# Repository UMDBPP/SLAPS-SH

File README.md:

# SLAPS-SH
The SLAPS Solar Harvester is intended as a the first step into solar power collection and management. While previous iterations in the SLAPS family have focused on solar panel deployment and configuration, the solar harvester focuses on collecting and managing the power generated by four solar panels. The primary device enabling this functionality is the AEM10941. This power harvesting IC collects power from the panels, regulates the power to multiple useful voltage levels, and charges a storage unit. This design required minimal passive components allowing for a low cost and space efficient design. In addition to the power harvesting circuit, the solar harvester will also feature a RP2040 microcontroller, altitude rated pressure-temperature sensor, and NAND flash for data logging. These additional components will provide an adequate test for the harvester capabilities. In order to leverage the space efficient nature of the electrical configuration, the structural construction of the solar harvester focuses on tight tolerances using 3D printed components. Maximizing the space efficiency of the solar harvester improves aesthetics and maximizes the flight line configurations that the solar harvester can fly on. Overall, this design will provide a realistic and maximally space efficient test of a solar harvesting circuit that could potentially be used in future SLAPS iterations.

## Electrical Overview
### AEM10941
The AEM10941 features multiple preset configurations as well as a custom mode. In this design, the configuration profile `111` is used by pulling the three configuration pins high. This configuration is designed for use with a Li-ion battery as the storage source and 3.3V and 1.8V outputs. The decision to use a Li-ion battery primarily comes from the need for a 3.3V output.

Quiescent current is expected to be roughly [0.6 \ \mu A](tex://0.6 \ \mu A) at a battery voltage of roughly 3.6V. The efficiency of the linear drop-out regulators are as follows:
- High-voltage: 80-90%
- Low-voltage: 70-80%

Overall, the losses experienced in the AEM10941 are relatively low in comparison to the power consumption of the device as a whole.

### RP2040
The RP2040 microcontroller is an incredibly popular Arduino compatible microcontroller with excellent design resources.

### MS560702BA03-50
The MS560702BA03-50 barometric pressure and temperature sensor designed to operate from [10](tex://10) to [1200 \ mbar](tex://1200 \ mbar) and [-40](tex://-40) to [85 \ \degree C](tex://85 \ \degree C). These values fall within typical launch conditions and this sensor should be able to provide barometric pressure and temperature values accurate to [\pm 2.5 mbar](tex://\pm 2.5 mbar) and [\pm 0.5 \ \degree C](tex://\pm 0.5 \ \degree C) for the duration of flight.

At a 3.3V supply voltage the MS560702BA03-50 has a peak power consumption of [4.62 \ mW](tex://4.62 \ mW) and a standby power consumption of [0.07 \ \mu W](tex://0.07 \ \mu W). Peak power consumption is unlikely to occur and typical power consumption at 1 sample/sec is expected to be less than [42 \ \mu W](tex://42 \ \mu W).

### Energy Storage
The solar harvester features one energy storage unit in the form of a single Li-ion battery cell.

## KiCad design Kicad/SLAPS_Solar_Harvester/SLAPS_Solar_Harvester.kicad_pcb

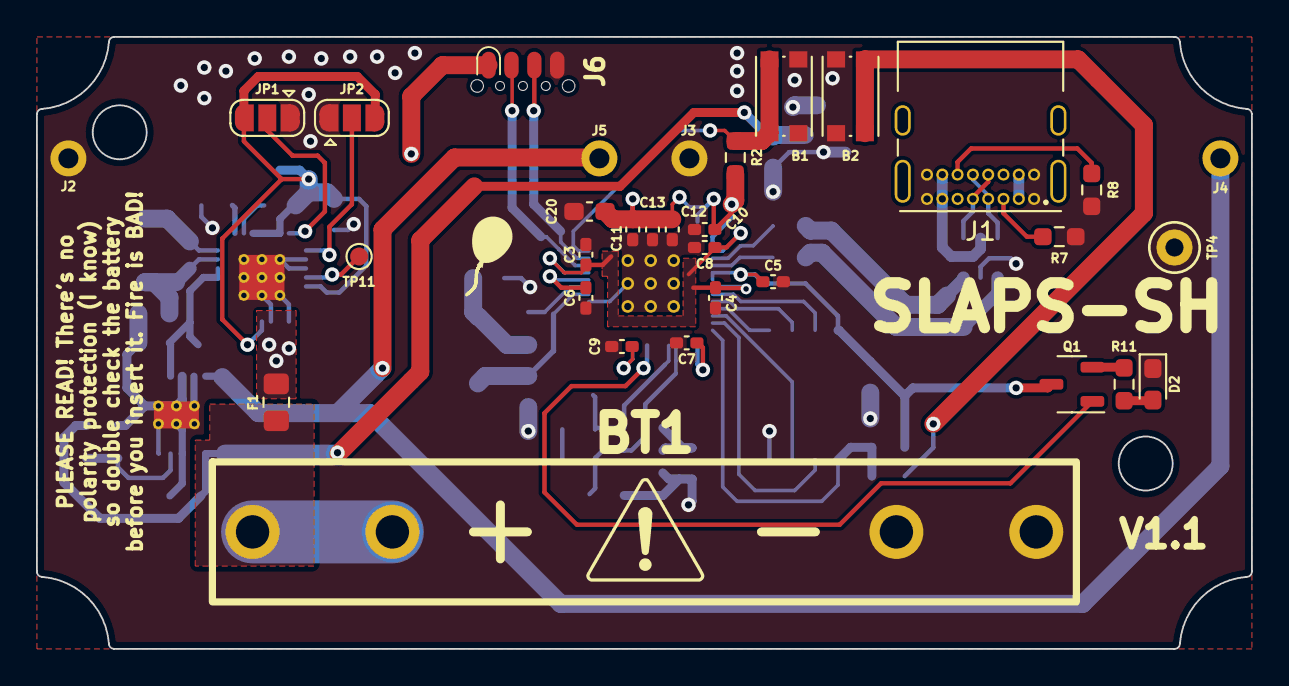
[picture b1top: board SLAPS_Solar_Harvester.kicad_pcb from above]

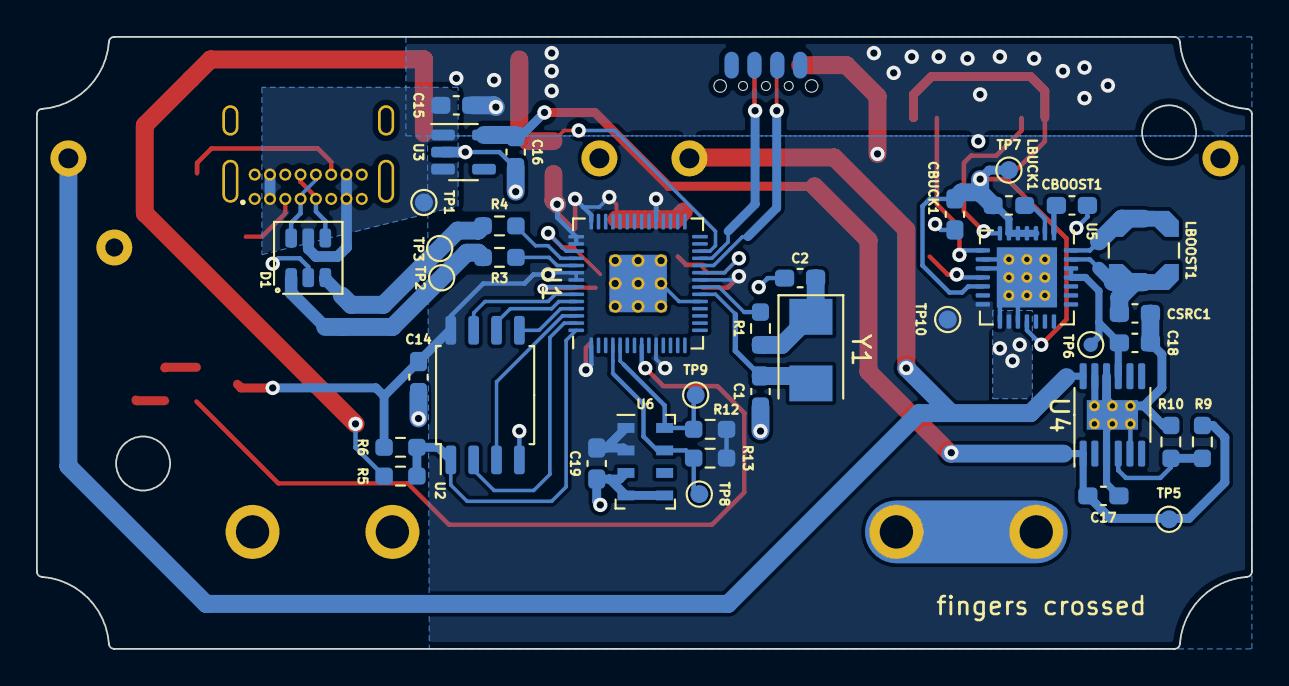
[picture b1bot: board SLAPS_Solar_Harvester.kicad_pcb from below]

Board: 2 copper layers, 67.5 x 34.0 mm, 71 parts (39 on the bottom side), 44 nets.

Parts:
B1, B2: KMR2; SW_Push_1P1T_NO_CK_KMR2
BT1: Battery_Cell; MPD_BK-82_x2
C1, C2: 27pF; C_0603_1608Metric_Pad1.08x0.95mm_HandSolder
C3, C4, C5, C6, C7, C9, C11, C12, C13: 100nF; C_0402_1005Metric_Pad0.74x0.62mm_HandSolder
C8, C10: 1uF; C_0402_1005Metric_Pad0.74x0.62mm_HandSolder
C14, C19: 100nF; C_0603_1608Metric_Pad1.08x0.95mm_HandSolder
C15, C16: 1uF; C_0603_1608Metric_Pad1.08x0.95mm_HandSolder
C17: 2.2uF; C_0603_1608Metric_Pad1.08x0.95mm_HandSolder
C18, C20: 10uF; C_0603_1608Metric_Pad1.08x0.95mm_HandSolder
CBOOST1: 22uF; C_0603_1608Metric_Pad1.08x0.95mm_HandSolder
CBUCK1: 22uF; C_0603_1608Metric_Pad1.08x0.95mm_HandSolder
CSRC1: 10uF; C_0603_1608Metric_Pad1.08x0.95mm_HandSolder
D1: USBLC6-2SC6; SOT-23-6
D2: LED; D_0603_1608Metric_Pad1.05x0.95mm_HandSolder
F1: Polyfuse_Small; Fuse_0805_2012Metric_Pad1.15x1.40mm_HandSolder
J1: USB_C_Receptacle_USB2.0; USB_C_Receptacle_GCT_USB4085
J2, J3, J4, J5: Conn_01x01_Male; P19-1121
J6: SOICbite; SOIC_clipProgSmall
JP1, JP2: SolderJumper_3_Open; SolderJumper-3_P1.3mm_Open_RoundedPad1.0x1.5mm
LBOOST1: 10uH; IND_LPS4012-103MRC
LBUCK1: 10uH; L_0603_1608Metric_Pad1.05x0.95mm_HandSolder
Q1: Q_NMOS_GSD; SOT-23-3
R1, R5: 1k; R_0603_1608Metric_Pad0.98x0.95mm_HandSolder
R2, R6, R12, R13: 10k; R_0603_1608Metric_Pad0.98x0.95mm_HandSolder
R3, R4: 27; R_0603_1608Metric_Pad0.98x0.95mm_HandSolder
R7, R8: 5.1k; R_0603_1608Metric_Pad0.98x0.95mm_HandSolder
R9: 1M; R_0603_1608Metric_Pad0.98x0.95mm_HandSolder
R10: 715k; R_0603_1608Metric_Pad0.98x0.95mm_HandSolder
R11: 590; R_0603_1608Metric_Pad0.98x0.95mm_HandSolder
TP1, TP2, TP3, TP5, TP6, TP7, TP8, TP9, TP10, TP11: TestPoint; TestPoint_Pad_D1.0mm
TP4: TestPoint; TestPoint_Keystone_5000-5004_Miniature
U1: RP2040; RP2040-QFN-56
U2: W25Q128JVS; SOIC-8_5.23x5.23mm_P1.27mm
U3: TPS7A0530PDBV; SOT-23-5
U4: LTC4419; MSOP-12-1EP_3x4mm_P0.65mm_EP1.65x2.85mm_ThermalVias
U5: AEM10941; QFN-28-1EP_5x5mm_P0.5mm_EP3.35x3.35mm_ThermalVias
U6: MS5607-02BA; LGA-8_3x5mm_P1.25mm
Y1: 445I23D12M00000; Crystal_SMD_5032-2Pin_5.0x3.2mm

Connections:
+1V1: C3.1, C4.1, C8.1, U1.23 (DVDD), U1.45 (VREG_VOUT), U1.50 (DVDD)
+1V8: TP11.1, U5.11 (LVOUT)
+3V0: C16.1, C17.1, R9.1, TP5.1, U3.5 (OUT), U4.1 (V1)
+3V3: C5.1, C6.1, C7.1, C9.1, C10.1, C11.1, C12.1, C13.1, C14.1, C19.1, C20.1, J6.1, Q1.3 (D), R2.1, R6.1, R12.1, R13.1, TP10.1, U1.1 (IOVDD), U1.10 (IOVDD), U1.22 (IOVDD), U1.33 (IOVDD), U1.42 (IOVDD), U1.43 (ADC_AVDD), U1.44 (VREG_IN), U1.48 (USB_VDD), U1.49 (IOVDD), U2.8 (VCC), U5.14 (HVOUT), U6.1 (VDD), U6.2 (PS)
/D1: Q1.1 (G), U1.8 (GPIO6)
/QSPI_SCLK: U1.52 (QSPI_SCLK), U2.6 (CLK)
/QSPI_SD0: U1.53 (QSPI_SD0), U2.5 (DI(IO0))
/QSPI_SD1: U1.55 (QSPI_SD1), U2.2 (DO(IO1))
/QSPI_SD2: U1.54 (QSPI_SD2), U2.3 (IO2)
/QSPI_SD3: U1.51 (QSPI_SD3), U2.7 (IO3)
/QSPI_SS: R5.2, R6.2, U1.56 (QSPI_SS), U2.1 (~CS)
/SCL: R12.2, TP9.1, U1.5 (GPIO3), U6.8 (SCLK)
/SDA: R13.2, TP8.1, U1.4 (GPIO2), U6.7 (SDI/SDA)
/SWCLK: J6.2, U1.24 (SWCLK)
/SWDIO: J6.3, U1.25 (SWD)
/USB_D+: D1.1 (L1), R3.2, TP2.1
/USB_D-: D1.3 (L2), R4.2, TP3.1
/VBUCK: CBUCK1.2, JP1.3 (B), JP2.3 (B), LBUCK1.1, TP7.1, U5.3 (BUCK), U5.4 (CFG[2]), U5.5 (CFG[1]), U5.6 (CFG[0]), U5.12 (ENHV), U5.18 (ENLV)
/VSRC: C18.1, TP6.1, U4.9 (OUT), U5.25 (SRC), U5.26 (FB_COLD)
GND: B1.1, B2.1, BT1.2 (-), C1.1, C2.1, C3.2, C4.2, C5.2, C6.2, C7.2, C8.2, C9.2, C10.2, C11.2, C12.2, C13.2, C14.2, C15.2, C16.2, C17.2, C18.2, C19.2, C20.2, CBOOST1.2, CBUCK1.1, CSRC1.2, D1.2 (VN), D2.1 (K), J1.A1 (GND), J1.A12 (GND), J1.B1 (GND), J1.B12 (GND), J2.1, J3.1, J6.4, JP1.1 (A), JP2.1 (A), R7.2, R8.2, R10.2, TP4.1, U1.19 (TESTEN), U1.57 (GND), U2.4 (GND), U3.2 (GND), U4.3 (CMP1), U4.5 (GND), U4.10 (CMP2), U4.11 (GND), U4.13 (GND), U5.9 (FB_PRIM_D), U5.10 (FB_PRIM_U), U5.15 (BAL), U5.17 (PRIM), U5.29 (GND), U6.3 (GND), U6.4 (CSB), U6.5 (CSB)
unnamed: B1.2, R2.2, U1.26 (RUN)
unnamed: B2.2, R5.1
unnamed: BT1.1 (+), F1.1
unnamed: C1.2, U1.20 (XIN), Y1.2
unnamed: C2.2, R1.1, Y1.1
unnamed: CBOOST1.1, U5.1 (BOOST)
unnamed: CSRC1.1, LBOOST1.1, U5.27 (BUFSRC)
unnamed: D1.4 (L2), J1.A7 (D-), J1.B7 (D-)
unnamed: D1.6 (L1), J1.A6 (D+), J1.B6 (D+)
unnamed: D2.2 (A), R11.2
unnamed: F1.2, U5.16 (BATT)
unnamed: J1.A5 (CC1), R7.1
unnamed: J1.B5 (CC2), R8.1
unnamed: J4.1, J5.1, U4.12 (V2)
unnamed: JP1.2 (C), U5.7 (SELMPP[1])
unnamed: JP2.2 (C), U5.8 (SELMPP[0])
unnamed: LBOOST1.2, U5.28 (SWBOOST)
unnamed: LBUCK1.2, U5.2 (SWBUCK)
unnamed: Q1.2 (S), R11.1
unnamed: R1.2, U1.21 (XOUT)
unnamed: R3.1, U1.47 (USB_DP)
unnamed: R4.1, U1.46 (USB_DM)
unnamed: R9.2, R10.1, U4.4 (ADJ)
VBUS: C15.1, D1.5 (VP), J1.A4 (VBUS), J1.A9 (VBUS), J1.B4 (VBUS), J1.B9 (VBUS), TP1.1, U3.1 (IN), U3.3 (EN)

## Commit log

2023-05-01 initial
2023-05-01 bootloader woes
2023-05-03 ughhhh
2023-05-04 this bootloader will be the end of me
2023-05-08 started on V1.1
2023-05-09 working on RP2040 rev
2023-05-12 some extras
2023-05-16 more work on V1.1
2023-05-18 more V1.1
2023-05-24 step file of board
2023-06-02 KiCad version 7
2023-07-01 Minimal firmware
2023-11-27 added reference pdf
